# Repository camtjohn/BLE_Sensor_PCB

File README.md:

# BLE_Sensor_PCB
kicad files for pcb

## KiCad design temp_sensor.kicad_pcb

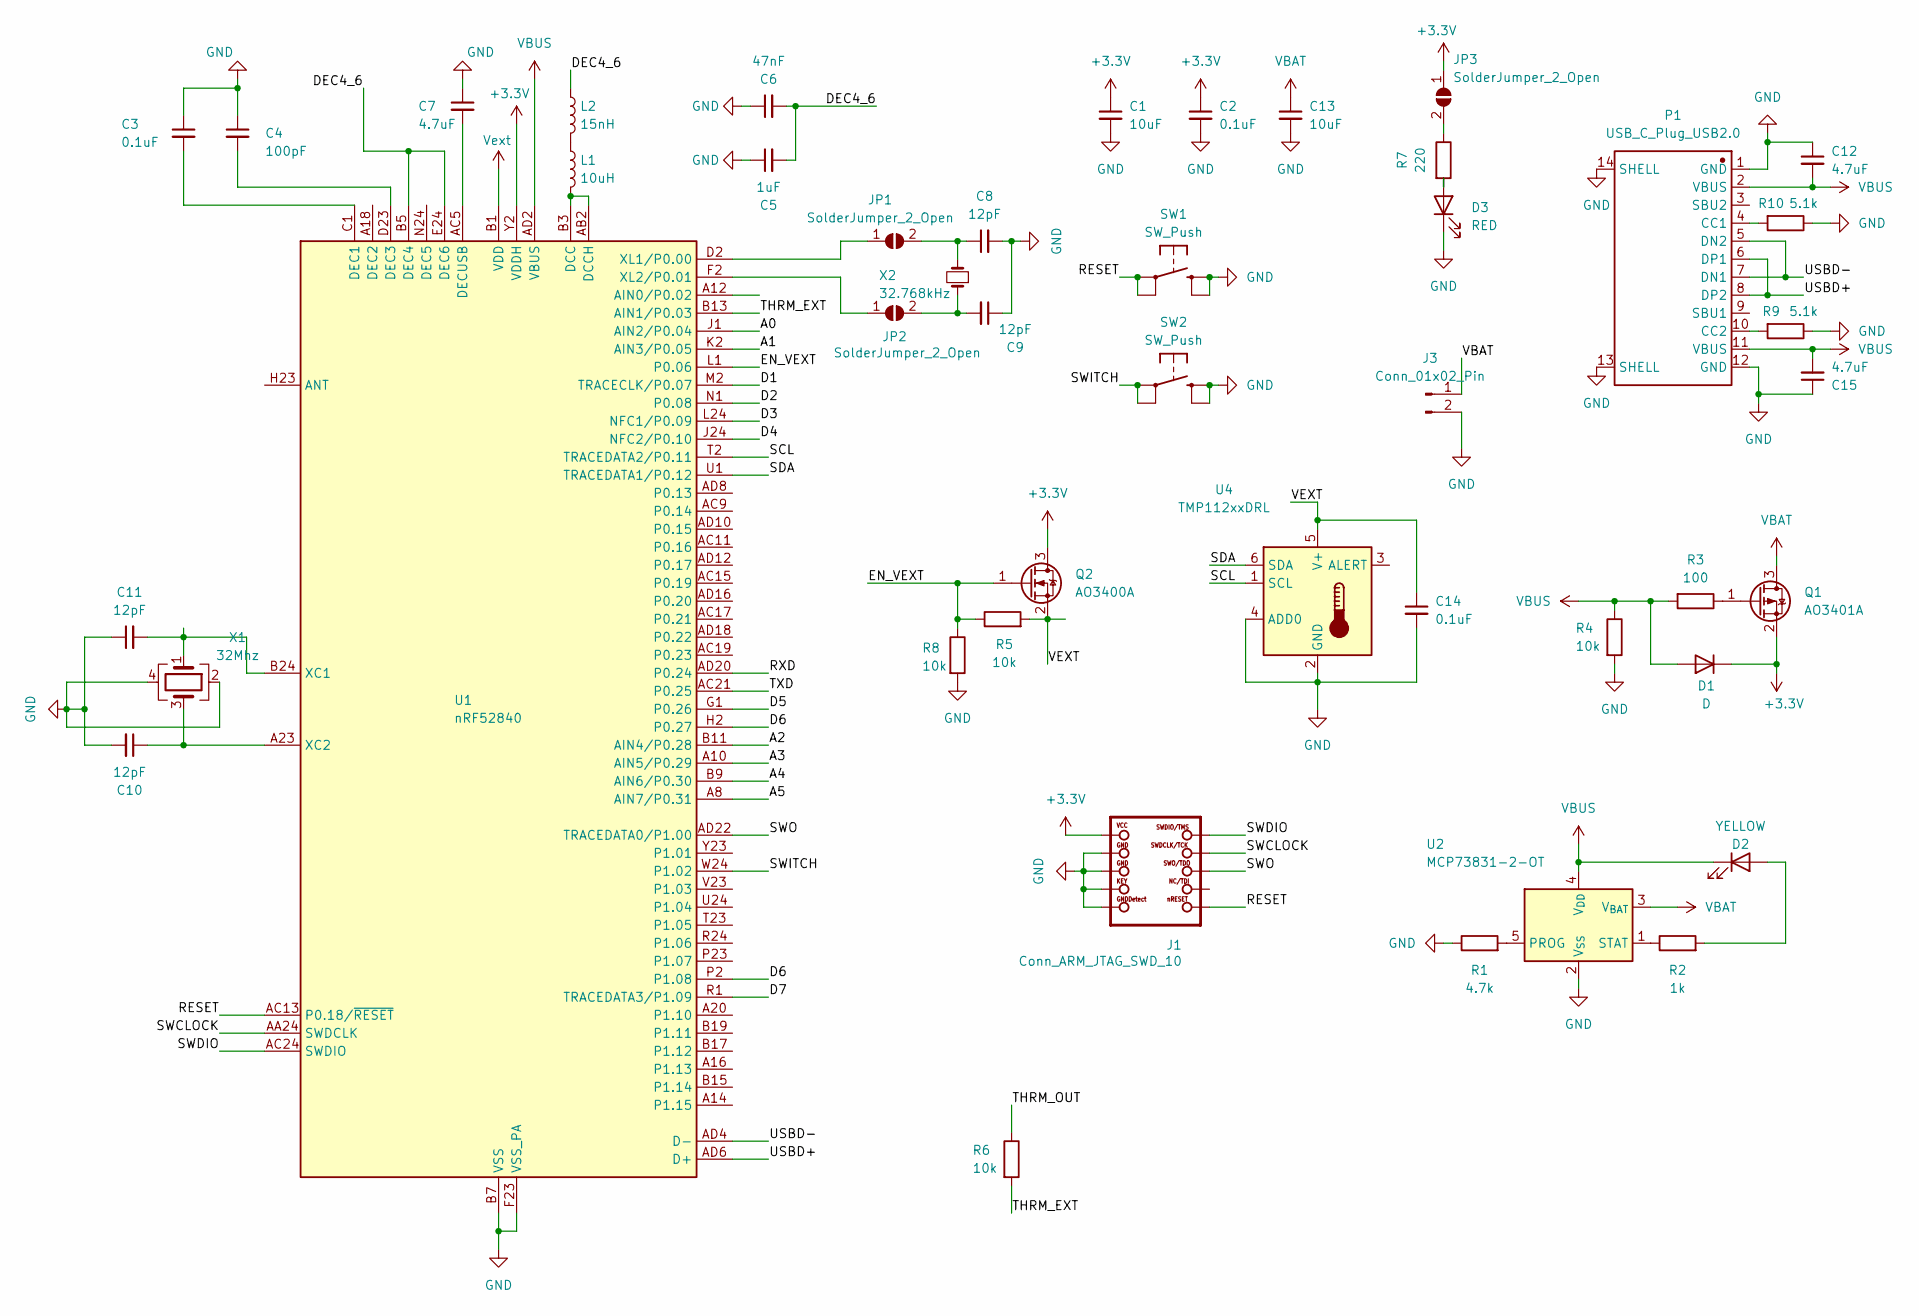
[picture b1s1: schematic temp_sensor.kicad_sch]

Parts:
C1, C13: 10uF; 0402_cap
C2, C3, C14: 0.1uF; 0402_cap
C4: 100pF; 0402_cap
C5: 1uF; 0402_cap
C6: 47nF; 0402_cap
C7, C12, C15: 4.7uF; 0402_cap
C8, C9, C10, C11: 12pF; 0402_cap
D1: D; SOD-123FL_diode
D2: YELLOW; 0805_led_yellow
D3: RED; 0603_led_red
J1: Conn_ARM_JTAG_SWD_10; Adafruit_JTAG_2X05_1.27MM_BOX_POSTS
J3: Conn_01x02_Pin; JST_PH_S2B-PH-K_1x02_P2.00mm_Horizontal
JP1, JP2, JP3: SolderJumper_2_Open; SolderJumper-2_P1.3mm_Open_RoundedPad1.0x1.5mm
L1: 10uH; 1206_cap
L2: 15nH; 0402_cap
P1: USB_C_Plug_USB2.0; USBC_custom
Q1: AO3401A; SOT-23
Q2: AO3400A; SOT-23
R1: 4.7k; 0603_res
R2: 1k; 0603_res
R3: 100; 0603_res
R4, R5, R6, R8: 10k; 0603_res
R7: 220; 0603_res
R9, R10: 5.1k; 0603_res
SW1, SW2: SW_Push; switch_modify
U1: nRF52840; Nordic_AQFN-73-1EP_7x7mm_P0.5mm
U2: MCP73831-2-OT; SOT-23-5
U4: TMP112xxDRL; SOT-563
X1: 32Mhz; XTAL_32mhz
X2: 32.768kHz; xtal_32_768khz

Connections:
+3.3V: C1.1, C2.1, D1.1 (C), J1.1 (VCC), JP3.1 (A), Q1.2 (S), Q2.3 (D), U1.Y2 (VDDH)
/A0: U1.J1 (AIN2/P0.04)
/A1: U1.K2 (AIN3/P0.05)
/A2: U1.B11 (AIN4/P0.28)
/A3: U1.A10 (AIN5/P0.29)
/A4: U1.B9 (AIN6/P0.30)
/A5: U1.A8 (AIN7/P0.31)
/D1: U1.M2 (TRACECLK/P0.07)
/D2: U1.N1 (P0.08)
/D3: U1.L24 (NFC1/P0.09)
/D4: U1.J24 (NFC2/P0.10)
/D5: U1.G1 (P0.26)
/D6: U1.H2 (P0.27), U1.P2 (P1.08)
/D7: U1.R1 (TRACEDATA3/P1.09)
/DEC4_6: C5.2, C6.2, L2.1, U1.B5 (DEC4), U1.E24 (DEC6)
/EN_VEXT: Q2.1 (G), R5.1, R8.1, U1.L1 (P0.06)
/RESET: J1.10 (NRESET), SW1.1, SW1.3, U1.AC13 (P0.18/~RESET)
/RXD: U1.AD20 (P0.24)
/SCL: U1.T2 (TRACEDATA2/P0.11), U4.1 (SCL)
/SDA: U1.U1 (TRACEDATA1/P0.12), U4.6 (SDA)
/SWCLOCK: J1.4 (SWDCLK), U1.AA24 (SWDCLK)
/SWDIO: J1.2 (SWDIO), U1.AC24 (SWDIO)
/SWITCH: SW2.1, SW2.3, U1.W24 (P1.02)
/SWO: J1.6 (SWO), U1.AD22 (TRACEDATA0/P1.00)
/THRM_EXT: R6.2, U1.B13 (AIN1/P0.03)
/THRM_OUT: R6.1
/TXD: U1.AC21 (P0.25)
/USBD+: P1.6 (DP1), P1.8 (DP2), U1.AD6 (D+)
/USBD-: P1.5 (DN2), P1.7 (DN1), U1.AD4 (D-)
/VEXT: C14.1, Q2.2 (S), R5.2, U4.5 (V+)
GND: C1.2, C2.2, C3.1, C4.1, C5.1, C6.1, C7.1, C8.2, C9.1, C10.2, C11.1, C12.1, C13.2, C14.2, C15.1, D3.1 (K), J1.3 (GND@1), J1.5 (GND@2), J1.7 (KEY), J1.9 (GNDDETECT), J3.2, P1.1 (GND), P1.12 (GND), P1.13 (SHELL), P1.14 (SHELL), R1.1, R4.2, R8.2, R9.1, R10.1, SW1.2, SW1.4, SW2.2, SW2.4, U1.B7 (VSS), U1.EP (VSS), U1.F23 (VSS_PA), U2.2 (V_{SS}), U4.2 (GND), U4.4 (ADD0), X1.2, X1.4
unnamed: D2.2 (A), R2.2
unnamed: D3.2 (A), R7.2
unnamed: JP1.1 (A), U1.D2 (XL1/P0.00)
unnamed: C8.1, JP1.2 (B), X2.2
unnamed: JP2.1 (A), U1.F2 (XL2/P0.01)
unnamed: C9.2, JP2.2 (B), X2.1
unnamed: JP3.2 (B), R7.1
unnamed: L1.1, L2.2
unnamed: P1.4 (CC1), R10.2
unnamed: P1.10 (CC2), R9.2
unnamed: Q1.1 (G), R3.1
unnamed: L1.2, U1.AB2 (DCCH), U1.B3 (DCC)
unnamed: C3.2, U1.C1 (DEC1)
unnamed: C4.2, U1.D23 (DEC3)
unnamed: C7.2, U1.AC5 (DECUSB)
unnamed: C11.2, U1.B24 (XC1), X1.1
unnamed: C10.1, U1.A23 (XC2), X1.3
unnamed: R1.2, U2.5 (PROG)
unnamed: R2.1, U2.1 (STAT)
VBAT: C13.1, J3.1, Q1.3 (D), U2.3 (V_{BAT})
VBUS: C12.2, C15.2, D1.2 (A), D2.1 (K), P1.2 (VBUS), P1.11 (VBUS), R3.2, R4.1, U1.AD2 (VBUS), U2.4 (V_{DD})
Vext: U1.A22 (VDD), U1.AD14 (VDD), U1.AD23 (VDD), U1.B1 (VDD), U1.W1 (VDD)

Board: 2 copper layers, 45 parts (0 on the bottom side), 38 nets, no tracks yet.

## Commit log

2024-06-14 Adding kicad files to repo
2024-06-15 Including report generated when added components to PCB
